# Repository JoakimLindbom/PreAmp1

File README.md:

PreAmp1 
=======

Collection of files related to my pre-amplifier project, based on DIY Audio circuits, Hifiberry DAC+ DSP, own circuit design as well ad 3D printed parts.
The aim is to make a lot of the functionality available with physical controls.

Contents
========
- [3D](#3D)
- [Functions](#Functions)
  - [Equaliser](#Equaliser)
- [License](#license)

# 3D
This contains a faceplate for the Raspberry Pi 4 as well as a very sturdy assembly for the volume control potentiometer, enabling it to be placed on its own PCB, away from the main amplifier PCB.

# Functions
## Equaliser
Class for controlling the HifiberryOS/Beocreate DSP functions for the equaliser, using websockets for real-time control.

# License
Copyright (c) Joakim Lindbom 2021-2022, GPLv3.

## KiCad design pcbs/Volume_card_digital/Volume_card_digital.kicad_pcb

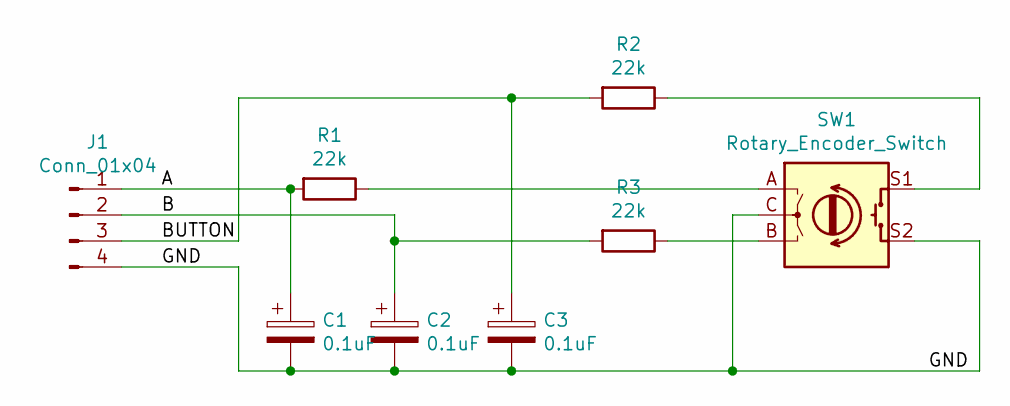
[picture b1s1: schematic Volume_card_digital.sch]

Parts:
C1, C2, C3: 0.1uF
J1: Conn_01x04
R1, R2, R3: 22k
SW1: Rotary_Encoder_Switch

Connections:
/A: C1.1, J1.1, R1.2
/B: C2.1, J1.2, R3.2
/BUTTON: C3.1, J1.3, R2.2
/GND: C1.2, C2.2, C3.2, J1.4, SW1.C, SW1.S2
unnamed: R1.1, SW1.A
unnamed: R2.1, SW1.S1
unnamed: R3.1, SW1.B

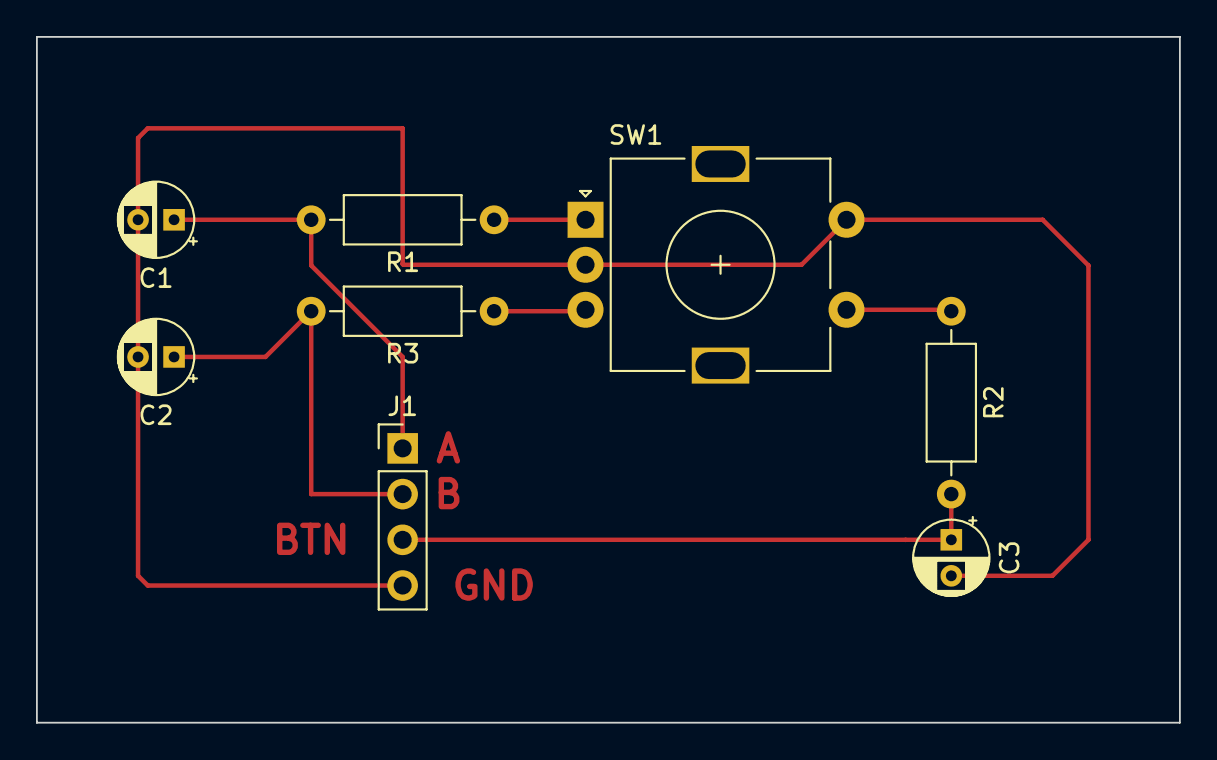
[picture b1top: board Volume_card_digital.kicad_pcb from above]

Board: 2 copper layers, 63.5 x 38.1 mm, 8 parts (0 on the bottom side), 7 nets.

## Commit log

2021-02-14 Added top view drawing of enclosure
2021-02-28 Updated drawings
2021-02-28 Added rotary encoder
2021-02-28 Debugging code
2021-02-28 Added Digital Volume PCB
2021-03-08 Changed layout
2021-03-13 Layout changes
2021-03-13 Volume control
2022-02-15 Added ST files for RPi face plate and holder
2022-02-21 Added first batch of software for the pre-amp"
2022-03-12 Added control of equaliser over websockets
2022-03-12 Moving files
2022-03-12 Added README
2022-03-13 Added preset handling
